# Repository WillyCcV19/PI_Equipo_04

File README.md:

# EQUIPO N° IV - Proyecto Integrador 2026-2  
<div align="center">

<!-- Banner animado (capsule-render funciona nativo en GitHub, sin GIFs pesados) -->

<!-- Texto tipo "máquina de escribir" (animado, se genera al vuelo) -->

<br/><br/>

</div>

### Carrera de Ingeniería Industrial / Informática   
**Universidad Peruana Cayetano Heredia**

---

## 👫 ¿Quiénes somos?

Somos participantes del curso Proyecto Integrador 2026-2, integrados por estudiantes de Ingeniería Industrial e Informática de la Universidad Peruana Cayetano Heredia. Nuestra misión es utilizar la metodología de diseño para desarrollar soluciones creativas y técnicamente fundamentadas que aporten valor social, tecnológico y ambiental.

---

## ⚙️  Justificación Técnica y Fundamento Biológico

Para validar técnicamente el desarrollo de FISHMON 365, nos basamos en la normativa e investigación oficial del Fondo Nacional de Desarrollo Pesquero (FONDEPES - PRODUCE, Perú) [1]:

### 1. Especie Cultivada y Taxonomía

- **Especie de crianza:** Trucha Arco Iris [1].
- **Nombre científico oficial:** *Oncorhynchus mykiss* (denominada anteriormente *Salmo gairdneri irideus*) [1].
- **Ambiente de cultivo:** Agua dulce continental (recursos hídricos lóticos como ríos, arroyos y manantiales, y lénticos como lagunas) [1].

### 2. Sistemas de Acuicultura en el Perú y Diagnóstico de Mortalidad

| Criterio Técnico | Sistema Convencional (Estanquería) | Sistema No Convencional (Jaulas Flotantes) |
|------------------|------------------------------------|---------------------------------------------|
| **Infraestructura principal** | Estanques de concreto, mampostería de piedra y tierra [1]. | Jaulas flotantes en lagos y lagunas [1]. |
| **Distribución Regional** | Mayor prevalencia en la Región Junín [1]. | Predominante en la Región Puno (concentra el 98% de esta modalidad) [1]. |
| **Aporte a la Producción Nacional (2012)** | Junín: 3,412.53 TM/Año (13.78%) [1]. | Puno: 18,471.02 TM/Año (74.59%) [1]. |
| **Variabilidad del Medio** | Altamente vulnerable a fluctuaciones de caudal, temperatura y arrastre de sólidos por lluvias [1]. | Vulnerable a eventos de anoxia global en la columna de agua y ecorregiones lénticas [1]. |

### 3. Causa Principal de Mortalidad: Asfixia e Hipoxia por Deficiencia de Oxígeno Disuelto (O₂)

La mayor tasa de mortandad o pérdida de rendimiento biológico-económico en los cultivos de trucha se debe a la pérdida del equilibrio entre el Hospedador, el Patógeno y el Ambiente ($H + P + A = E$) [1].

Específicamente, el factor crítico es la asfixia e hipoxia por baja concentración de oxígeno disuelto ($O_2$). De acuerdo con FONDEPES [1]:

> *"Como la crianza se realiza a grandes densidades es recomendable que la cantidad de oxígeno no sea menor a 5.5 mg/l (60% de saturación de oxígeno) en los momentos de máximo consumo en el cultivo, ya que de lo contrario los peces van a presentar signos de asfixia"* [1, p. 12].
>
> *"Pueden presentarse peces con hipoxia, aunque haya suficiente oxígeno en el medio de cultivo por la presencia de nitritos"* [1, p. 62].

---

## ⚙️ ¿En qué va a consistir el proyecto?

**FISHMON 365** es un **dispositivo multiparámetro portátil y autónomo** diseñado para el **monitoreo en tiempo real y a multinivel** de la calidad del agua dulce en sistemas de cultivo de trucha (*Oncorhynchus mykiss*) [1]. 

El sistema está compuesto por una **sección flotante con electrónica blindada** y una **sonda sumergible vertical multinivel**, equipada con sensores calibrados para realizar lecturas continuas a tres profundidades distintas dentro de la columna de agua. Toda la información capturada es procesada y transmitida de forma inalámbrica mediante tecnología **IoT** directamente a una **aplicación móvil para smartphone**, enviando alertas tempranas en tiempo real ante variaciones fuera de los rangos seguros [1].

Para garantizar la continuidad operativa en zonas rurales o ante posibles cortes de energía eléctrica, el equipo integra un **sistema de alimentación autónomo con batería de respaldo**, asegurando mediciones ininterrumpidas las 24 horas del día.

---

### Perfil de Medición Multinivel en la Columna de Agua

Dado que parámetros críticos como el oxígeno disuelto y la temperatura varían verticalmente según la dinámica del estanque, la descomposición de materia orgánica y el nivel de alimentación [1], **FISHMON 365** monitorea tres estratos clave:

| Profundidad / Estrato | Justificación Técnica Biológica | Impacto en la Trucha Arco Iris |
| :--- | :--- | :--- |
| **Superficie** | Zona de mayor intercambio gaseoso atmosférico e incidencia de radiación solar [1]. | Evalúa la temperatura máxima y la saturación inicial de oxígeno [1]. |
| **Nivel Medio (Media Agua)** | Zona de natación activa y desplazamiento del cardumen de truchas en crecimiento [1]. | Garantiza que la masa de agua habitada mantenga tenores de $O_2 \ge 5.5\text{ mg/L}$ [1]. |
| **Nivel de Fondo (Suelo acuícola)** | Zona de acumulación de alimento no consumido, heces, materia orgánica y alimentación del pez [1]. | Detecta zonas anóxicas ($O_2 < 3.0\text{ mg/L}$), acumulación de nitritos y variaciones de pH por descomposición [1]. |

---

## 🌿 Contexto de Aplicación y Validación de Campo: Santa Eulalia

Para validar el prototipo en condiciones reales de campo de la sierra de Lima, el dispositivo se probará en las piscigranjas de agua dulce del distrito de Santa Eulalia (Provincia de Huarochirí, Lima):

- **Ubicación de prueba:** Valle del río Santa Eulalia (Afluente del río Rímac).
- **Altitud de evaluación:** Entre 1,036 m.s.n.m. y 1,400 m.s.n.m. (zona de cuenca media).
- **Características hídricas:** Aguas continentales dulceacuícolas lóticas (ríos y arroyos de deshielo/manantial) [1].
- **Impacto ambiental local:** Permite monitorear la variación de temperatura y oxígeno disuelto en temporadas de estiaje vs. avenidas (lluvias), previniendo el estrés branquial y mortandades masivas [1].

---

## 🌿 ¿Qué problemáticas soluciona?

| Problema Actual en la Truchicultura | Solución Técnica que Aporta FISHMON 365 | Sustento Oficial (FONDEPES) |
|--------------------------------------|------------------------------------------|-----------------------------|
| Altas mortandades por asfixia silenciosa ($O_2 < 5.5\text{ mg/L}$) | Monitoreo continuo de Oxígeno Disuelto con alertas sonoras/visuales inmediatas. | *"A menores niveles de $O_2$ (0 - 3.0 mg/l), la trucha muere; entre 3.1 - 4.5 mg/l sufre grave estrés"* [1, p. 12]. |
| Elevados costos de equipos comerciales de laboratorio | Diseño portátil de bajo costo con componentes e integración local | Permite acceso a tecnología a productores de subsistencia y menor escala ($99.44\%$ del mercado) [1, p. 9]. |
| Mediciones manuales extemporáneas que no previenen crisis | Lectura inmediata en campo con diagnóstico automático vía IoT | Permite ajustar inmediatamente la tasa de recambio de agua por hora (R/A/H) [1, p. 11]. |
| Falta de conectividad en zonas altoandinas/rurales | Funcionamiento en modo offline con almacenamiento SD y sincronización posterior IoT | Asegura el registro histórico sin depender de cobertura celular continua. |
| Falta de estandarización técnica del criador | Configuración de umbrales bajo la NTP y manuales de PRODUCE/FONDEPES | Ajustado a los rangos óptimos del agua para *Oncorhynchus mykiss* [1, p. 12-13]. |

---

## 🌿 Alineación con Objetivos de Desarrollo Sostenible (ODS)

Nos comprometemos con la agenda global incorporando las metas oficiales ajustadas según la fuente de la Organización de las Naciones Unidas (ONU):

### 🌿 ODS 9: Industria, Innovación e Infraestructura

**Meta 9.5:** *Aumentar la investigación científica y mejorar la capacidad tecnológica de los sectores industriales de todos los países, en particular los países en desarrollo, entre otras cosas fomentando la innovación e incrementando considerablemente de aquí a 2030 el número de personas que trabajan en investigación y desarrollo por millón de habitantes y los gastos en investigación y desarrollo de los sectores público y privado.*

### 🌿 ODS 12: Producción y Consumo Responsables

**Meta 12.a:** *Ayudar a los países en desarrollo a fortalecer su capacidad científica y tecnológica para avanzar hacia modalidades de consumo y producción más sostenibles.*

### 🌿 ODS 14: Vida Submarina y Recursos Hídricos

**Meta 14.7:** *De aquí a 2030, aumentar los beneficios económicos que los pequeños Estados insulares en desarrollo y los países menos adelantados obtienen del uso sostenible de los recursos marinos, en particular mediante la gestión sostenible de la pesca, la acuicultura y el turismo.*

**Meta 14.a:** *Aumentar los conocimientos científicos, desarrollar la capacidad de investigación y transferir tecnología marina, teniendo en cuenta los Criterios y Directrices para la Transferencia de Tecnología Marina de la Comisión Oceanográfica Intergubernamental, a fin de mejorar la salud de los océanos y potenciar la contribución de la biodiversidad marina al desarrollo de los países en desarrollo, en particular los pequeños Estados insulares en desarrollo y los países menos adelantados.*

---

## 🌿 Matriz de Parámetros Técnicos de Medición (Agua Dulce)

Basado estrictamente en las especificaciones del Manual de Cultivo de Trucha - FONDEPES [1]:

| Parámetro Fisicoquímico | Rango Crítico / Letal | Rango Óptimo de Cultivo | Impacto Biológico en la Trucha Arco Iris |
|--------------------------|------------------------|--------------------------|-------------------------------------------|
| **Oxígeno Disuelto ($O_2$)** | $< 3.0\text{ mg/L}$ (Muerte)<br>$3.1 - 4.5\text{ mg/L}$ (Estrés grave) [1] | **$6.0 - 8.5\text{ mg/L}$** (Mínimo $5.5\text{ mg/L}$) [1] | La deficiencia causa asfixia, reducción del consumo de alimento y suspensión del crecimiento [1]. |
| **Temperatura ($T^\circ\text{C}$)** | $< 3^\circ\text{C}$ o $> 20^\circ\text{C}$ (Muerte / Riesgo severo) [1] | **$11 - 16^\circ\text{C}$** (Engorde óptimo: $15 - 16^\circ\text{C}$)<br>(Incubación: $8 - 10^\circ\text{C}$) [1] | Condiciona el metabolismo, apetito, velocidad de crecimiento y solubilidad del oxígeno disuelto [1]. |
| **Potencial de Hidrógeno (pH)** | $< 6.0$ o $> 9.0$ (Incompatible con la vida) [1] | **$7.0 - 8.0$** (Ligeramente alcalino) [1] | Niveles $< 6.5$ producen hemorragias branquiales y mortandades masivas [1]. |
| **Turbidez / Sólidos** | Elevados sólidos en suspensión [1] | Agua cristalina / Filtrada [1] | Los sólidos en suspensión dañan las branquias y sofocan a los alevinos [1]. |
| **Dióxido de Carbono ($CO_2$)** | $> 2.0\text{ ppm}$ [1] | $< 2.0\text{ ppm}$ [1] | Concentraciones altas merman el $O_2$ disuelto y alteran el pH sanguíneo del pez [1]. |

---

## 📷 Fotografía del equipo

---

## 👫 Integrantes

| Foto | Nombre | Rol | Intereses |
|------|--------| --- | --------- |
|  | **Karita John Kenneth** | **Líder / Diseñador** | **Diseño de prototipos, hardware** |
|  | **Cabrera Cermeno Ruben Andre** | **Desarrollo de sistemas** | **Tecnología e implementación de programas** |
|  | **Ccatamayo Vasquez Willy Simeon** | **Programador / Modelador** | **Programación, simulación** |
|  | **Pauccara Huancara Eber** | **Encargado de Documentación** | **Producción de documentos científicos y técnicos** |
|  | **Quispitongo Leon Verenisse Mary**|  **Responsable de investigación** | **Gestión ambiental, desarrollo comunitario** |

---
##  Fotografía esperada del producto

---

##  Referencias Bibliográficas

1. **Fondo Nacional de Desarrollo Pesquero (FONDEPES).** (2013). *Manual de Cultivo de Trucha en Ambientes Convencionales*. Ministerio de la Producción (PRODUCE), Dirección General de Capacitación y Desarrollo Técnico en Acuicultura. Lima, Perú. 87 pp.
2. **Organización de las Naciones Unidas (ONU).** (2015). *Transformar nuestro mundo: la Agenda 2030 para el Desarrollo Sostenible*. Resolución aprobada por la Asamblea General el 25 de septiembre de 2015 (A/RES/70/1).

---

<p align="center">
  <strong>🐟 FISHMON 365 — Monitoreo inteligente para una acuicultura sostenible</strong>
</p>
<p align="center">
  <sub>© 2026 - Universidad Peruana Cayetano Heredia</sub>
</p>

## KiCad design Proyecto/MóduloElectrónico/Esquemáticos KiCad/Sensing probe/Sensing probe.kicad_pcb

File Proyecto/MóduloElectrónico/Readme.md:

# Bill of materials (no necesariamente del esquemático presente en la carpeta)
- Sensor de oxígeno disuelto gravity
- 2x amplificadores CA3140
- 1x amplificador LM324N
- 2x transceptores LoRa V4 ... por especificar más
- 1x arduino nano
- 4x baterías 18650 1000mA (encontré varios en una laptop)
- respectivo socket paralelo
- módulo de carga
- 4x convertidores boost MT3608
- 1x regulador 7805 + circuito filtrado
- varios componentes pasivos (resistencias, capacitores)
- Conectores MOLEX varios ... por especificar más
- Motor paso a paso ... 28BYJ48 + ULN2003?
- Sensores IR de parada ... Por verse, se acoplarán con encoder
- Pin headers y pin sockets 2.54mm

## Esquemático en KiCAD

## Renderizado 3D

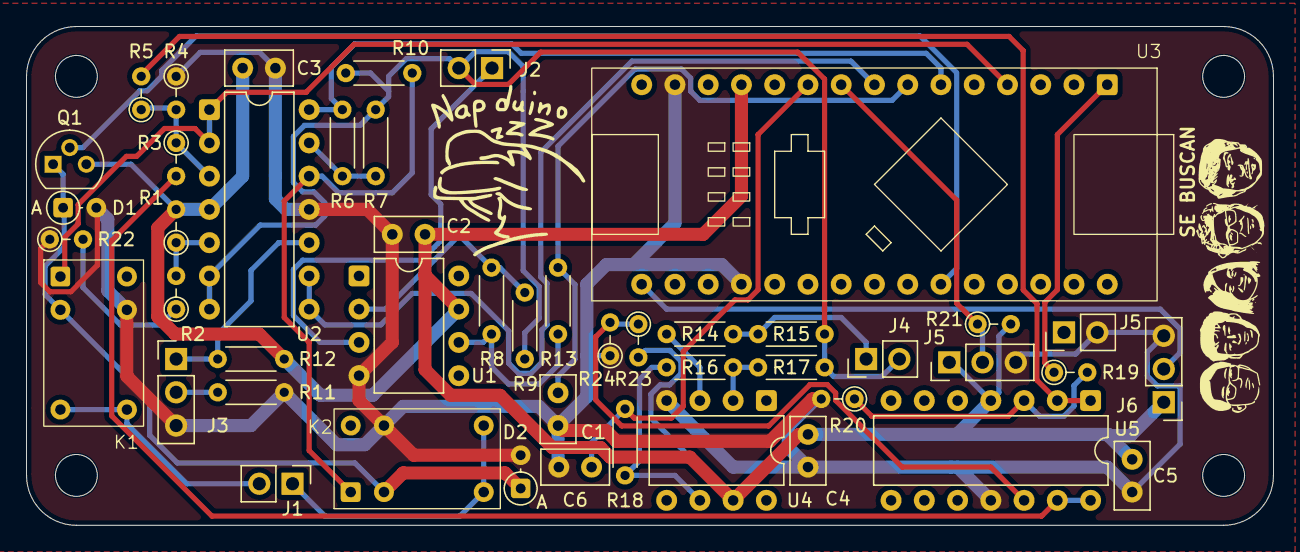
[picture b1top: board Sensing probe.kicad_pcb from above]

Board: 2 copper layers, 95.2 x 38.1 mm, 47 parts (0 on the bottom side), 33 nets.

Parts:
C1, C2, C3, C4, C5: 100n; C_Disc_D5.0mm_W2.5mm_P2.50mm
C6: 10n; C_Disc_D5.0mm_W2.5mm_P2.50mm
D1, D2: 1N4007; D_DO-34_SOD68_P2.54mm_Vertical_AnodeUp
J1, J2, J4, J5#2: Conn_01x02; PinHeader_1x02_P2.54mm_Vertical
J3, J5, J6: Conn_01x03_Pin; PinHeader_1x03_P2.54mm_Vertical
K1, K2: HFD23
Q1: Q_NPN_EBC; TO-92
R1, R3, R4, R19, R21, R23: 10K; R_Axial_DIN0204_L3.6mm_D1.6mm_P2.54mm_Vertical
R2: 3.3K; R_Axial_DIN0204_L3.6mm_D1.6mm_P2.54mm_Vertical
R5: 33K; R_Axial_DIN0204_L3.6mm_D1.6mm_P2.54mm_Vertical
R6, R8: 50K; R_Axial_DIN0204_L3.6mm_D1.6mm_P5.08mm_Horizontal
R7, R9, R13: 10K; R_Axial_DIN0204_L3.6mm_D1.6mm_P5.08mm_Horizontal
R10: 150; R_Axial_DIN0204_L3.6mm_D1.6mm_P5.08mm_Horizontal
R11: 5K; R_Axial_DIN0204_L3.6mm_D1.6mm_P5.08mm_Horizontal
R12: 510; R_Axial_DIN0204_L3.6mm_D1.6mm_P5.08mm_Horizontal
R14: 4.7K; R_Axial_DIN0204_L3.6mm_D1.6mm_P5.08mm_Horizontal
R15: 7.5K; R_Axial_DIN0204_L3.6mm_D1.6mm_P5.08mm_Horizontal
R16: 300K; R_Axial_DIN0204_L3.6mm_D1.6mm_P5.08mm_Horizontal
R17: 8.2K; R_Axial_DIN0204_L3.6mm_D1.6mm_P5.08mm_Horizontal
R18: 220; R_Axial_DIN0204_L3.6mm_D1.6mm_P5.08mm_Horizontal
R20, R24: 15K; R_Axial_DIN0204_L3.6mm_D1.6mm_P2.54mm_Vertical
R22: 1K; R_Axial_DIN0204_L3.6mm_D1.6mm_P2.54mm_Vertical
U1, U4: CA3140; DIP-8_W7.62mm
U2, U5: LM324; DIP-14_W7.62mm
U3: Arduino nano

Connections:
+5V: C2.1, C3.1, C4.1, C5.1, J5.1, J6.1, Q1.3 (C), R1.2, R12.1, R21.2, R23.2, U1.7 (V+), U2.4 (V+), U3.12 (5V), U4.7 (V+), U5.4 (V+)
/1.5V: J2.2, J4.2, R7.2, R9.2, R10.2, R15.2, R17.2, U2.6 (-), U2.7
/3V: R3.2, U5.13 (-), U5.14
/COND: R6.1, U2.14, U3.6 (A2)
/COND_READ: K2.13, R10.1, U2.12 (+)
/DO: C6.1, R18.1, U3.10 (A6)
/ELECTRODE_A: J1.2, K1.11
/ELECTRODE_B: J1.1, K2.11
/PH: C1.1, R13.1, U3.7 (A3)
/PULSE: R19.1, U3.1 (D13)
/RELAY: Q1.2 (B), U3.25 (D7)
/SIGNAL: K1.13, U2.1, U2.2 (-), U3.4 (A0)
/TEMP: J5.2, R21.1, U3.9 (A5)
/TURB: U2.8, U2.9 (-), U3.8 (A4)
/TX: J6.2, U3.16 (TX1)
GND: C1.2, C2.2, C3.2, C4.2, C5.2, C6.2, D1.2 (A), D2.2 (A), J3.3, J5.3, J5#2.2, J6.3, K1.A2, K2.A2, R4.1, R11.2, R20.2, R22.1, R24.1, U1.4 (V-), U2.11 (V-), U3.14 (GND), U3.19 (GND), U4.4 (V-), U5.11 (V-)
unnamed: D1.1 (K), D2.1 (K), K1.A1, K2.A1, Q1.1 (E)
unnamed: J2.1, U1.3 (+)
unnamed: J3.1, R12.2, U2.10 (+)
unnamed: J3.2, R11.1
unnamed: J4.1, R14.2, R15.1
unnamed: R2.1, R22.2
unnamed: R8.1, R13.2, U1.6
unnamed: R16.1, R18.2, U4.6
unnamed: R8.2, R9.1, U1.2 (-)
unnamed: R3.1, R4.2, R5.1, U2.3 (+)
unnamed: R1.1, R2.2, U2.5 (+)
unnamed: R6.2, R7.1, U2.13 (-)
unnamed: R14.1, U4.3 (+)
unnamed: R16.2, R17.1, U4.2 (-)
unnamed: R19.2, R20.1, U5.3 (+)
unnamed: R5.2, U5.1, U5.2 (-)
unnamed: R23.1, R24.2, U5.12 (+)

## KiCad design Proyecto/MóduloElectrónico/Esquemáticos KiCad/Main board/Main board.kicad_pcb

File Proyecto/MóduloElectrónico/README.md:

## ESQUEMA NO TERMINADO - INICIAL
## Falta colocar más detalles, PCB, grupo, curso, etc

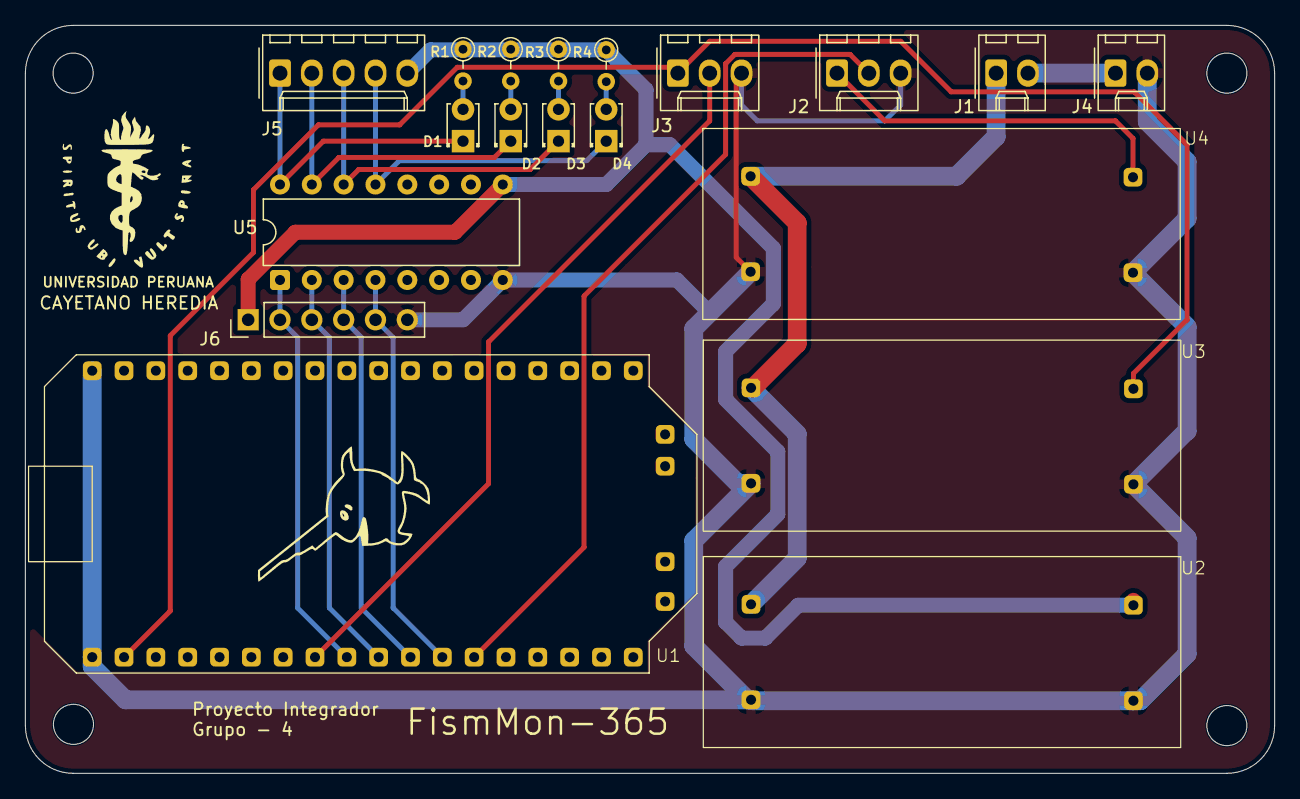
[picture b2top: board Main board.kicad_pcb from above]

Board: 2 copper layers, 99.7 x 59.7 mm, 19 parts (0 on the bottom side), 20 nets.

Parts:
D1, D2, D3, D4: LED; LED_D1.8mm_W3.3mm_H2.4mm
J1, J4: Conn_01x02_Pin; Molex_KK-254_AE-6410-02A_1x02_P2.54mm_Vertical
J2, J3: Conn_01x03_Pin; Molex_KK-254_AE-6410-03A_1x03_P2.54mm_Vertical
J5: Conn_01x05_Pin; Molex_KK-254_AE-6410-05A_1x05_P2.54mm_Vertical
J6: Conn_01x06_Pin; PinHeader_1x06_P2.54mm_Vertical
R1, R2, R3, R4: 510; R_Axial_DIN0204_L3.6mm_D1.6mm_P2.54mm_Vertical
U1: LoRa-V4-Heltec
U2, U3, U4: mt-3608
U5: ULN2003; DIP-16_W7.62mm

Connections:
/M0: J6.2, U1.9 (GPIO-36), U5.1 (I1)
/M1: J6.3, U1.10 (GPIO-35), U5.2 (I2)
/M2: J6.4, U1.11 (GPIO-34), U5.3 (I3)
/M3: J6.5, U1.12 (GPIO-33), U5.4 (I4)
/MCU_5V: J3.1, U1.2 (5V), U3.4 (VOUT+)
/MOTOR_5V: J5.5, J6.1, R1.1, R2.1, R3.1, R4.1, U2.4 (VOUT+), U5.9 (COM)
/ROTATION_INFO: J3.2, U1.8 (GPIO-0)
/SENSOR_5V: J2.1, U4.4 (VOUT+)
/SENSOR_COMM: J2.2, U1.13 (GPIO-47)
GND: J2.3, J3.3, J4.2, J6.6, U1.1 (GND), U1.36 (GND), U2.2 (GND), U2.3 (GND), U3.2 (GND), U3.3 (GND), U4.2 (GND), U4.3 (GND), U5.8 (GND)
unnamed: D1.2 (A), R1.2
unnamed: D1.1 (K), J5.1, U5.16 (O1)
unnamed: D2.2 (A), R2.2
unnamed: D2.1 (K), J5.2, U5.15 (O2)
unnamed: D3.2 (A), R3.2
unnamed: D3.1 (K), J5.3, U5.14 (O3)
unnamed: D4.2 (A), R4.2
unnamed: D4.1 (K), J5.4, U5.13 (O4)
unnamed: J1.1, U2.1 (VIN+), U3.1 (VIN+), U4.1 (VIN+)
unnamed: J1.2, J4.1

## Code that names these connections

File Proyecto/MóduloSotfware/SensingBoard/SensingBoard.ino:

#include <OneWire.h>
#include <DallasTemperature.h>
#define SENSOR_PIN 9
OneWire oneWire(SENSOR_PIN);
DallasTemperature sensors(&oneWire);

uint8_t signal = A0;    // Señal de excitación
uint8_t ref = A1;       // Referencia
uint8_t cond = A2;      // Lectura de conductividad
uint8_t ph = A3;        // Lectura de PH
uint8_t turb = A4;      // Lectura de Turbidez
uint8_t d_o = A5;       // Lectura de oxígeno disuelto
uint8_t relay = 7;      // Pin de desactivación de sensor de conductividad
float m_res = 150;      // Valor de resistencia para sensor de conductividad
uint8_t pulse = 13;     // Pin para pulso de excitación
uint16_t adc = 1023;    // Precisión del ADC

float v_ref;            // Voltaje de referencia
float v_pou;            // Voltaje de pulso
float v_out;            // Voltaje de salida de sensor de conductividad
float resistencia;      // Resistencia leída del sensor de conductividad
float turbidez;         // Voltaje del sensor de turbidez
float pothid;           // Voltaje del sensor de PH
float temperatura;      // Temperatura
float oxigeno_dis;      // Oxígen disuelto


float read_cond(){                          // Leer una muestra de conductividad
  v_ref = 5.0 *  analogRead(ref) / adc;     // Leer voltaje de referencia 
  v_pou = 5.0 *  analogRead(signal) / adc;  // Leer voltaje de pulso
  v_out = 5.0 *  analogRead(cond) / adc;    // Leer voltaje de salida
  return ((150.0 * (v_pou - v_ref)) / ((v_out - v_ref) / 6)) - 150.0;    // Retornar el valor de la resistencia
}


float get_conductivity(){
  uint8_t counter = 0;
  float acc = 0;
  digitalWrite(relay, HIGH);      // Activar el relé
  delay(10);                      // Esperar a que los contactos peguen
  while(counter != 250){          // Repetir 250 veces (cada iteración dura ~ 2 milisegundos)
    digitalWrite(pulse, HIGH);    // Pulso de excitación
    delay(1);                     // Delay de pulso
    acc = acc + read_cond();      // Leer conductividad
    digitalWrite(pulse, LOW);
    delay(1);
    acc = acc + read_cond();
    counter ++;                   // Incrementar contador
  }
  digitalWrite(relay, LOW);       // Desactivar el relé
  return (acc / 500.0);           // Retornar valor promediado de conductividad
}

float get_turbidity(){
  float acc = 0;
  float temp = 0;
  uint8_t counter = 0;

  while(counter != 250){          // Repetir 250 veces (cada iteración dura ~ 1 milisegundo)
    temp = float(5.0 * analogRead(turb) / adc);  // Leer sensor de turbidez
    acc = acc + temp;             // Acumular valor de voltaje
    delay(1);                     // Delay de lectura
    counter ++;
  }
  return acc / 250;               // Retornar voltaje promediado del sensor de turbidez
}

float get_do(){
  float acc = 0;
  float temp = 0;
  uint8_t counter = 0;

  while(counter != 250){          // Repetir 250 veces (cada iteración dura ~ 1 milisegundo)
    temp = float(5.0 * analogRead(d_o) / adc);  // Leer sensor de turbidez
    acc = acc + temp;             // Acumular valor de voltaje
    delay(1);                     // Delay de lectura
    counter ++;
  }
  return acc / 250;               // Retornar voltaje promediado del sensor de oxígeno disuelto
}

float get_ph(){
  float acc = 0;
  float temp = 0;
  uint8_t counter = 0;

  while(counter != 250){          // Repetir 250 veces (cada iteración dura ~ 1 milisegundo)
  temp = (5.0*(analogRead(ph) - analogRead(ref)))/(2.5*adc);  // Leer sensor de ph
    acc = acc + temp;
    delay(1);                     // Delay de lectura
    counter ++;
  }

  return acc / 250;               // Retornar voltaje promediado del sensor de ph
}

float get_temperature(){          // No tengo idea, para haber sido de chat GPT funciona bien
  sensors.requestTemperatures();
  float temperatura = sensors.getTempCByIndex(0);
  if(temperatura < -30){
    sensors.begin();
  }
  return temperatura;
}

void setup() {
  sensors.begin();               // Iniciar el sensor de temperatura
  pinMode(relay, OUTPUT);        // Asignar pin de salida para relé
  pinMode(pulse, OUTPUT);        // Asignar pin de salida para pulso de excitación
  Serial.begin(115200);          // Inicializar terminal serial a 11520 baudios
}

void loop() {
  //resistencia = get_conductivity();  // Llamar la función de lectura de conductividad
  //temperatura = get_temperature();   // Llamar la función de lectura de temperatura
  //turbidez = get_turbidity();
  //pothid = get_ph();
  //oxigeno_dis = get_do();

  delay(1000);
  //Serial.println();
  //Serial.print("Resistencia: ");
  //Serial.print(resistencia);
  //Serial.println();
  //Serial.print("Temperatura: ");
  //Serial.print(temperatura);
  //Serial.println();
  //Serial.print("Turbidez: ");
  //Serial.print(turbidez);
  //Serial.println();
  //Serial.print("pH: ");
  //Serial.print(pothid);
  //Serial.println();
  //Serial.print("Oxígeno disuelto: ");
  //Serial.print(oxigeno_dis);
  //Serial.println();

  Serial.begin(9600, SERIAL_8N1);
  byte datos[5] = {10, 25, 100, 200, 255};
  Serial.write(datos, 5);
}

// Falta colocar una función para leer oxígeno disuelto
// Voltajes de ph y turbidez no calibrados
// Calibrar sensor de conductividad
// Ver Benson-Krausevoid setup() {
